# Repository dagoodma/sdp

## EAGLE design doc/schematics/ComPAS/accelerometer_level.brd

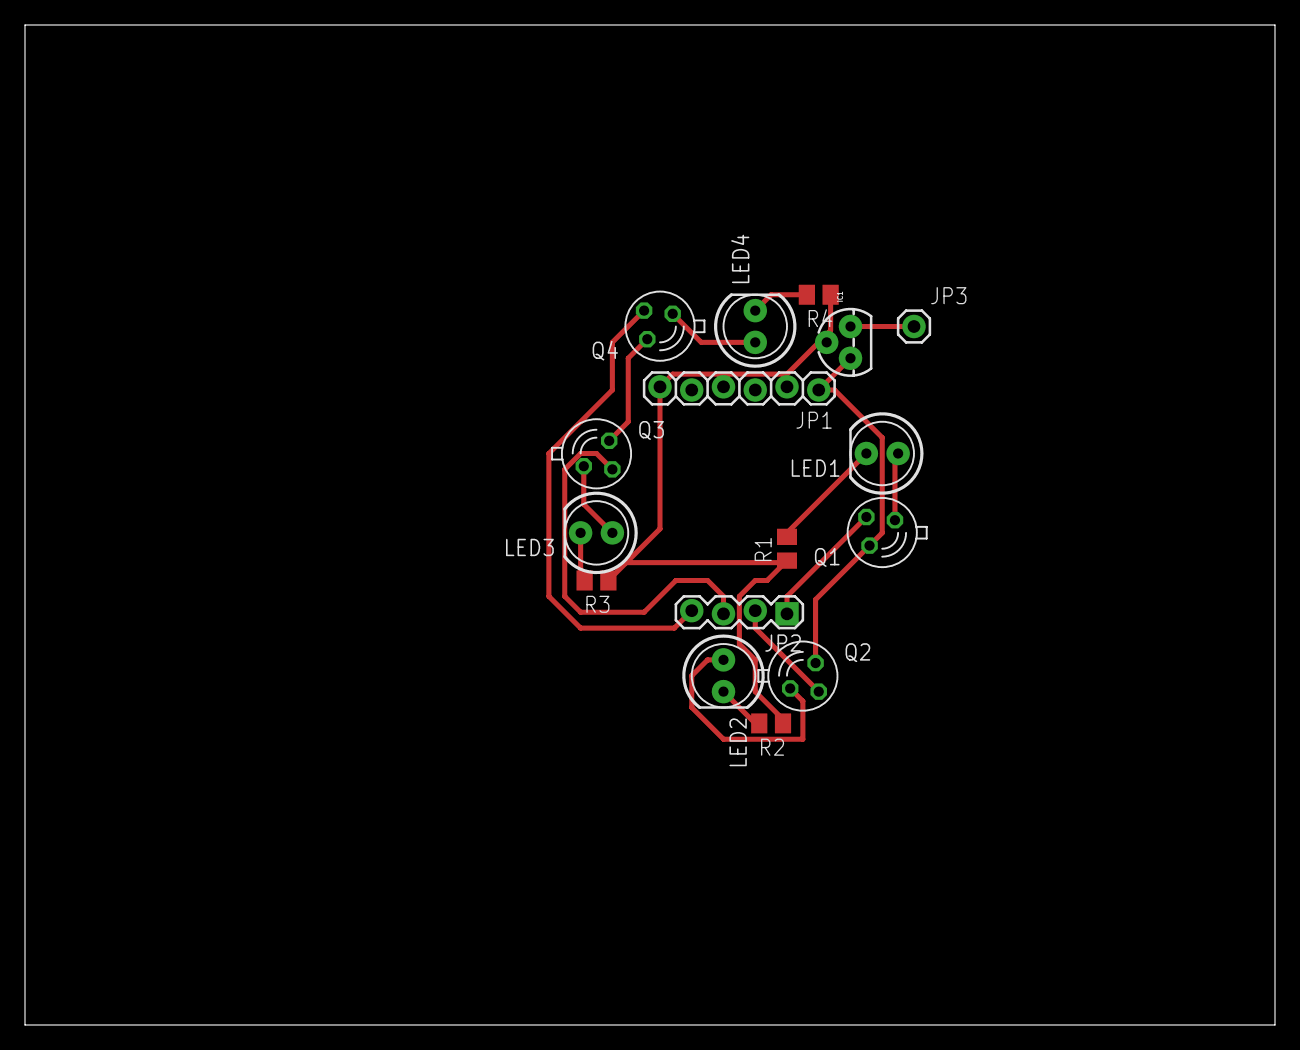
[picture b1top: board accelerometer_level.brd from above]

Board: 2 copper layers, 100.0 x 80.0 mm, 16 parts (0 on the bottom side), 15 nets.

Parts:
IC1: TO-92
JP1: 1X06_LOCK
JP2: 1X04_LOCK
JP3: M01PTH; 1X01
LED1, LED2, LED3, LED4: LED5MM
Q1, Q2, Q3, Q4: BP103
R1, R2, R3, R4: 100; M0805

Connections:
+3V3A: IC1.1, JP1.1, Q1.C, Q2.C, Q3.C, Q4.C
GND: IC1.2, JP1.6, R1.1, R2.1, R3.1, R4.1
unnamed: LED1.K, R1.2
unnamed: LED2.K, R2.2
unnamed: LED3.K, R3.2
unnamed: LED4.K, R4.2
unnamed: LED1.A, Q1.E
unnamed: LED2.A, Q2.E
unnamed: LED3.A, Q3.E
unnamed: LED4.A, Q4.E
unnamed: JP2.1, Q1.B
unnamed: JP2.2, Q2.B
unnamed: JP2.3, Q3.B
unnamed: JP2.4, Q4.B
unnamed: IC1.3, JP3.1

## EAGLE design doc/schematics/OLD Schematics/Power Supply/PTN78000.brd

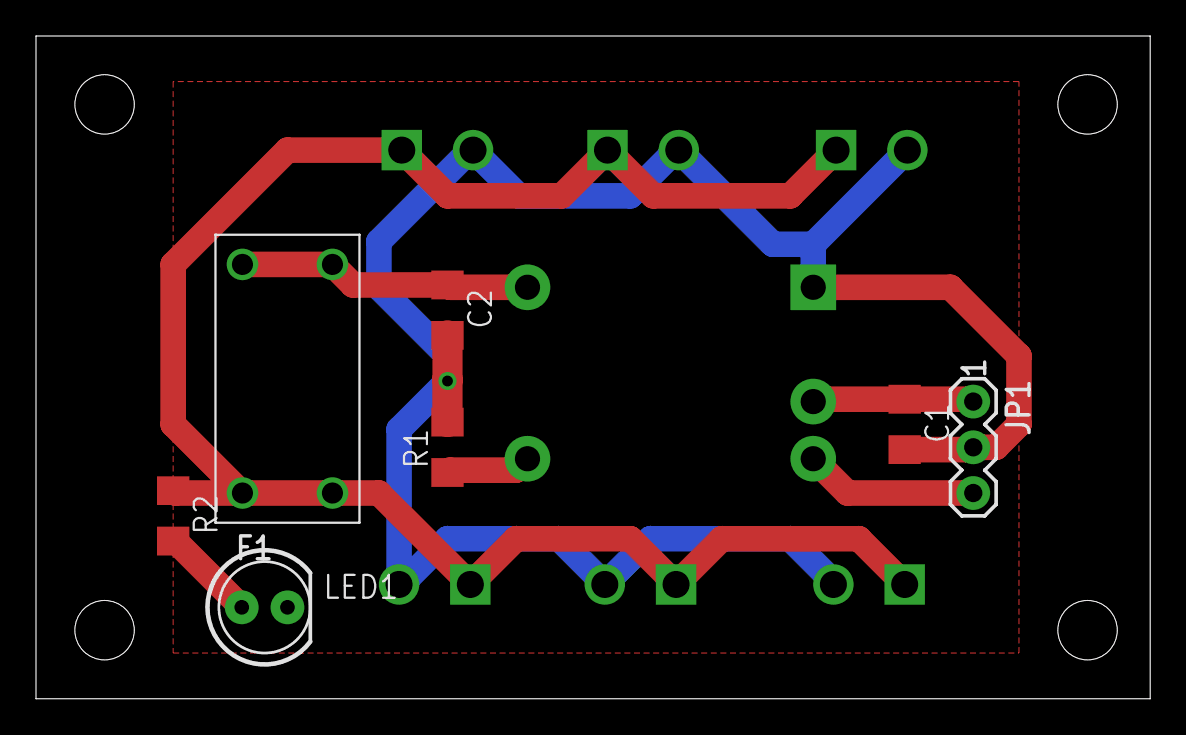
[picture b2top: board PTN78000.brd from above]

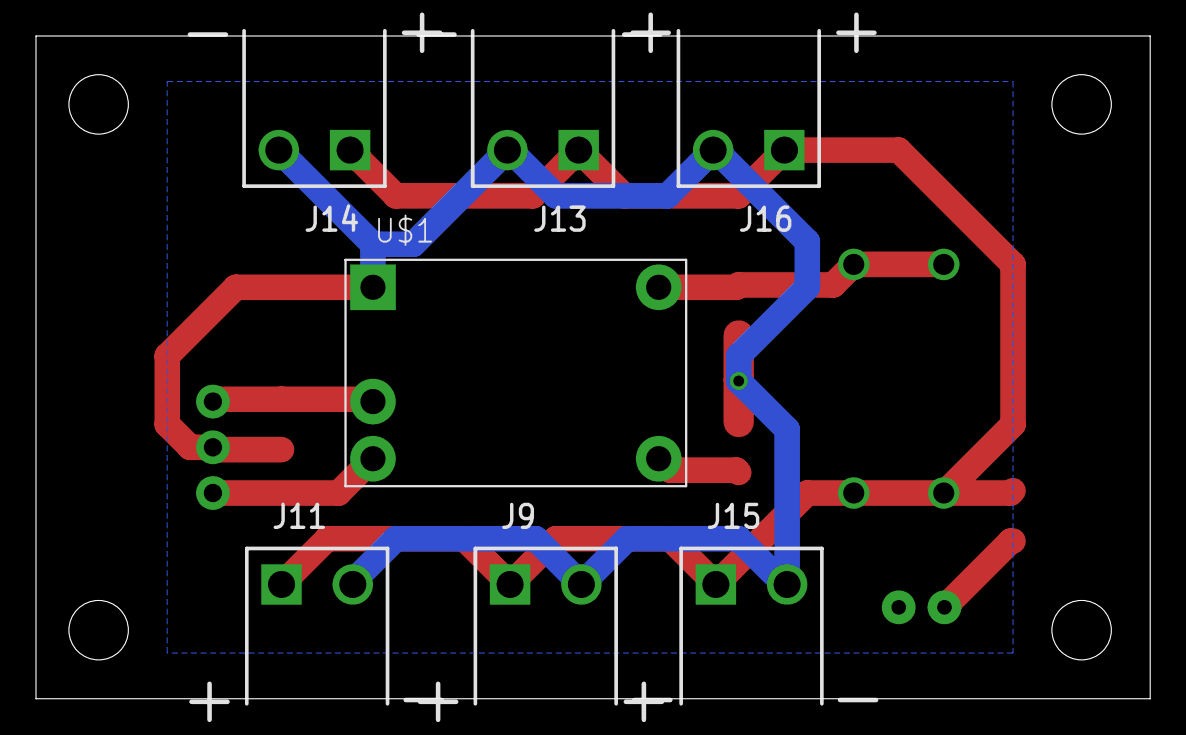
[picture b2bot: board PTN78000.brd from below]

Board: 2 copper layers, 61.9 x 36.8 mm, 18 parts (7 on the bottom side), 7 nets.

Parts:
C1: 2.2 uF; 1206
C2: 100 uF; 1206
F1: FUSE; FUSE_2AG
J9, J11, J13, J14, J15, J16: POW_CONNECTFEMALE-RA; SOCKET-FEMALE_RA-3.96MM-2
JP1: M03PTH; 1X03
LED1: LED5MM
R1: 21 K; 1206
R2: 330; 1206
U$1: PTN78000THROUGH-HOLE; PTN78000
U$6, U$11, U$12, U$13: STAND-OFF

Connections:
GND: C1.2, C2.2, J9.2, J11.2, J13.2, J14.2, J15.2, J16.2, JP1.2, LED1.K, R1.2, U$1.GND
unnamed: C1.1, JP1.1, U$1.V_IN
unnamed: R1.1, U$1.ADJ
unnamed: JP1.3, U$1.INHIBIT
unnamed: C2.1, F1.P$1, F1.P$2, U$1.V_OUT
unnamed: LED1.A, R2.2
VCC5V0: F1.P$3, F1.P$4, J9.1, J11.1, J13.1, J14.1, J15.1, J16.1, R2.1

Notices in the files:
parts and their libraries:
SparkFun-Connectors: Licensing: CC v3.0 Share-Alike You are welcome to use this library for commercial purposes.
